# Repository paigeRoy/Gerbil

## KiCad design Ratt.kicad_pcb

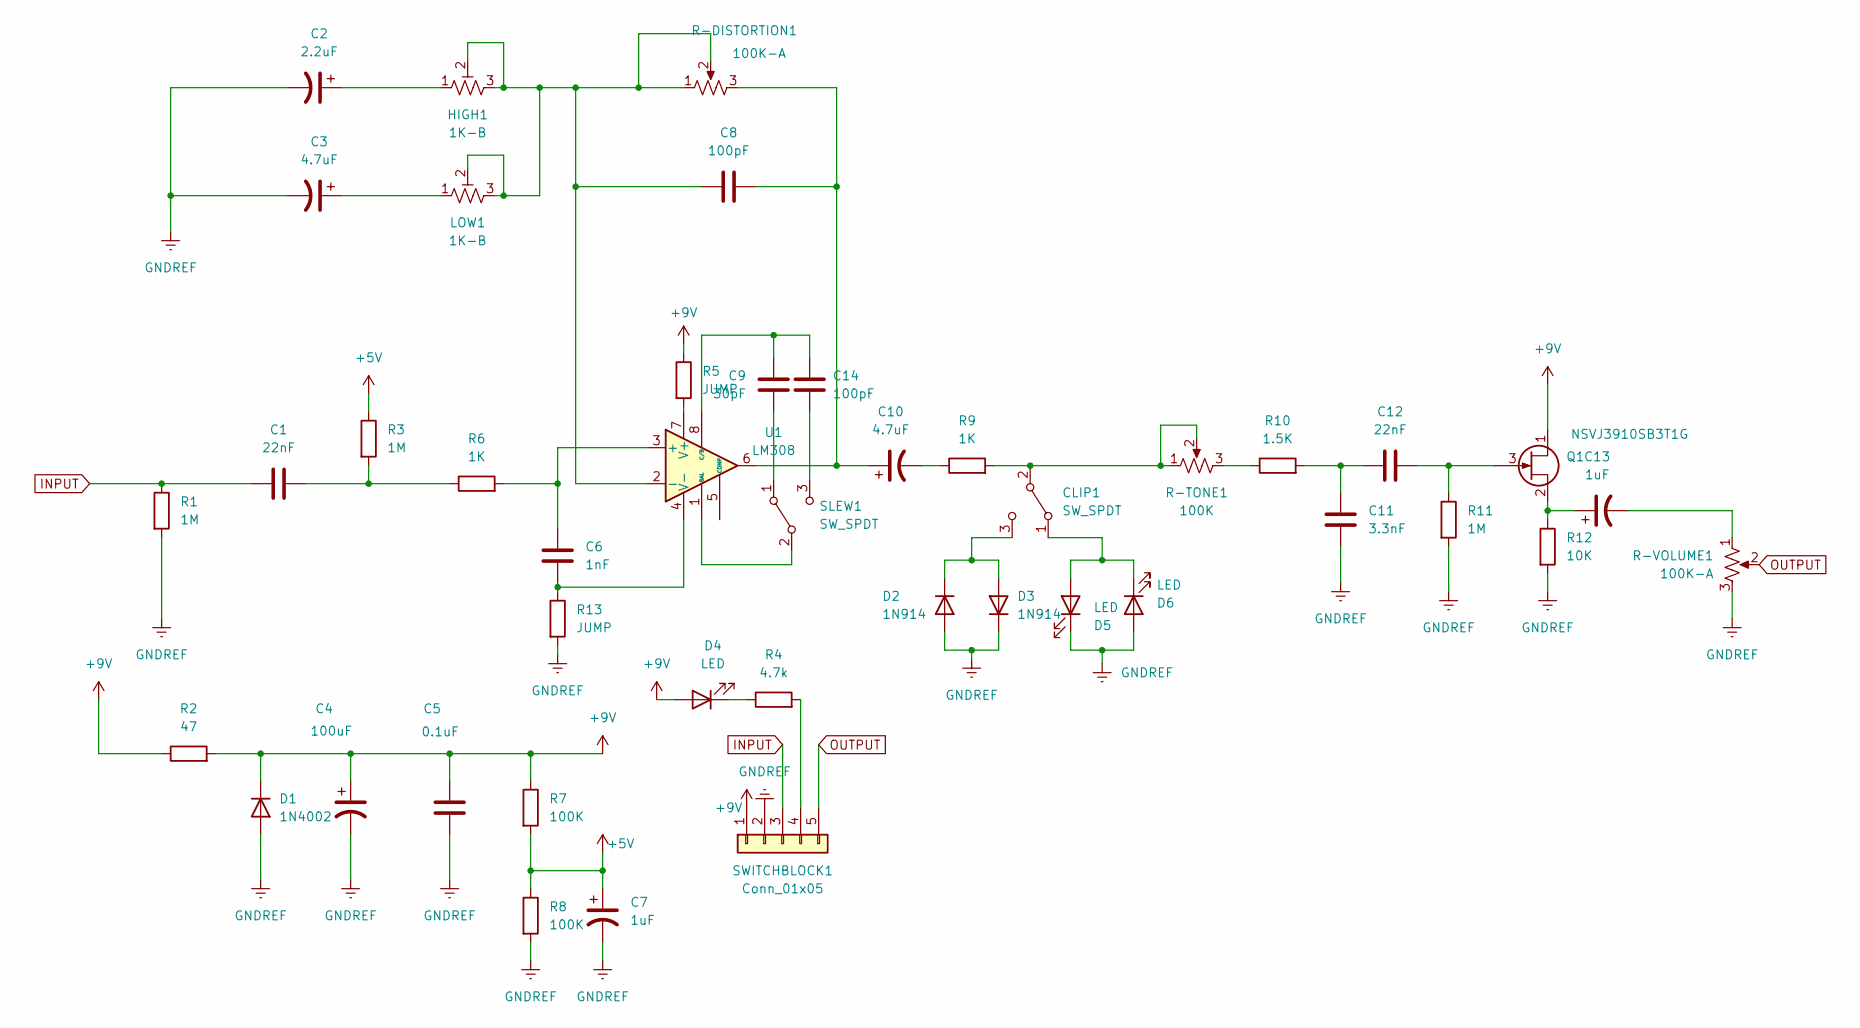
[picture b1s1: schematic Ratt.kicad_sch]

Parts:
C1, C12: 22nF; C_0805_2012Metric
C2: 2.2uF; CP_Elec_4x5.7
C3, C10: 4.7uF; CP_Elec_4x5.7
C4: 100uF; CP_Radial_D8.0mm_P3.50mm
C5: 0.1uF; C_0805_2012Metric
C6: 1nF; C_0805_2012Metric
C7, C13: 1uF; CP_Radial_D6.3mm_P2.50mm
C8, C14: 100pF; C_0805_2012Metric
C9: 30pF; C_0805_2012Metric
C11: 3.3nF; C_0805_2012Metric
CLIP1: SW_SPDT; BASIC_POT
D1: 1N4002; D_DO-41_SOD81_P7.62mm_Horizontal
D2, D3: 1N914; D_SOD-123F
D4, D5, D6: LED; SLR-343
HIGH1: 1K-B; Potentiometer_Runtron_RM-065_Vertical
LOW1: 1K-B; Potentiometer_Runtron_RM-065_Vertical
Q1: NSVJ3910SB3T1G; SC-59
R1, R3, R11: 1M; R_0805_2012Metric
R2: 47; R_0805_2012Metric
R4: 4.7k; R_0805_2012Metric
R5, R13: JUMP; R_0805_2012Metric
R6, R9: 1K; R_0805_2012Metric
R7, R8: 100K; R_0805_2012Metric
R10: 1.5K; R_0805_2012Metric
R12: 10K; R_0805_2012Metric
R-DISTORTION1: 100K-A; BASIC_POT
R-TONE1: 100K; BASIC_POT
R-VOLUME1: 100K-A; BASIC_POT
SLEW1: SW_SPDT; BASIC_POT
SWITCHBLOCK1: Conn_01x05; 3DPDT_SWITCHING
U1: LM308; SOIC-8-1EP_3.9x4.9mm_P1.27mm_EP2.29x3mm

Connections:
+5V: C7.1, R3.1, R7.2, R8.1
+9V: C4.1, C5.1, D1.1 (K), D4.2 (A), Q1.1 (D), R2.1, R2.2, R5.1, R7.1, SWITCHBLOCK1.1
GNDREF: C2.2, C3.2, C4.2, C5.2, C7.2, C11.2, D1.2 (A), D2.2 (A), D3.1 (K), D5.1 (K), D6.2 (A), R1.2, R8.2, R11.2, R12.2, R13.2, R-VOLUME1.3, SWITCHBLOCK1.2
INPUT: C1.1, R1.1, SWITCHBLOCK1.3
unnamed: C1.2, R3.2, R6.1
unnamed: C2.1, HIGH1.1
unnamed: C3.1, LOW1.1
unnamed: C6.1, R6.2, U1.3 (+)
unnamed: C6.2, R13.1, U1.4 (V-)
unnamed: C8.1, HIGH1.2, HIGH1.3, LOW1.2, LOW1.3, R-DISTORTION1.1, R-DISTORTION1.2, U1.2 (-)
unnamed: C9.1, SLEW1.1 (A)
unnamed: C9.2, C14.2, U1.8 (C/B)
unnamed: C8.2, C10.1, R-DISTORTION1.3, U1.6
unnamed: C11.1, C12.1, R10.2
unnamed: C13.2, R-VOLUME1.1
unnamed: CLIP1.1 (A), D5.2 (A), D6.1 (K)
unnamed: CLIP1.3 (C), D2.1 (K), D3.2 (A)
unnamed: D4.1 (K), R4.1
unnamed: C13.1, Q1.2 (S), R12.1
unnamed: C12.2, Q1.3 (G), R11.1
unnamed: C10.2, R9.1
unnamed: R10.1, R-TONE1.3
unnamed: CLIP1.2 (B), R9.2, R-TONE1.1, R-TONE1.2
unnamed: C14.1, SLEW1.3 (C)
unnamed: R4.2, SWITCHBLOCK1.4
unnamed: SLEW1.2 (B), U1.1 (BAL)
unnamed: R5.2, U1.7 (V+)
OUTPUT: R-VOLUME1.2, SWITCHBLOCK1.5

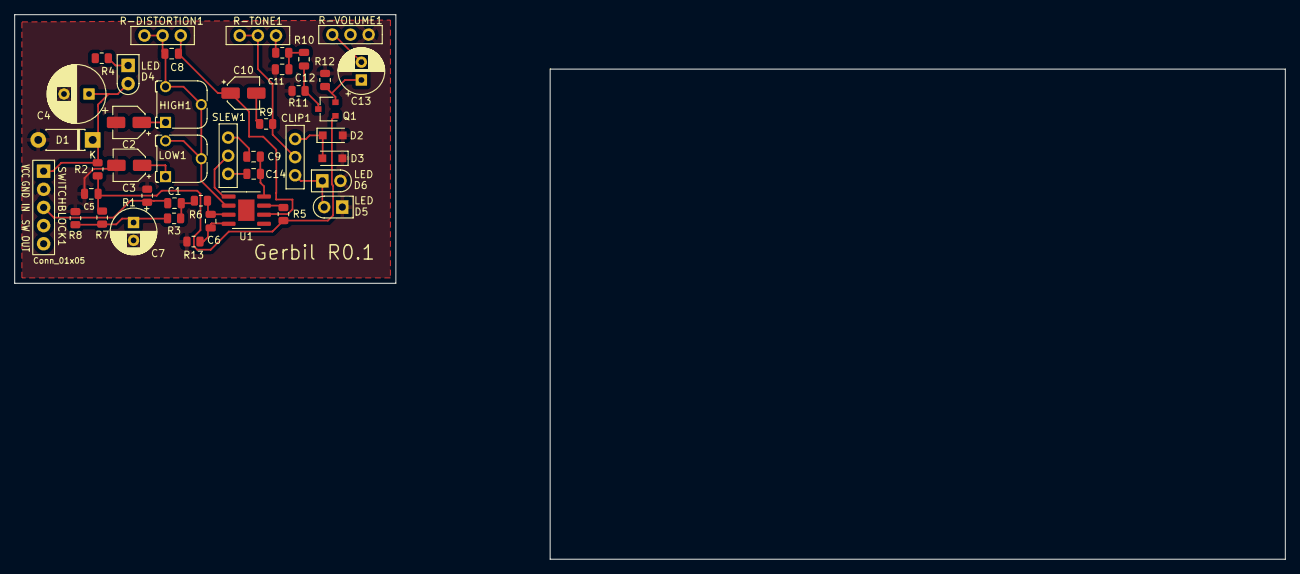
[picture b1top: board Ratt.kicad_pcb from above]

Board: 2 copper layers, 177.8 x 76.2 mm, 43 parts (0 on the bottom side), 28 nets.

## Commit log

2023-11-22 Added REV0.1 KiCad files
    Current revision on the board
2023-11-22 Gerbers exported
    more information in Readme later lol
